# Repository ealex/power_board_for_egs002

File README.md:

# power_board_for_egs002
a power board for EGS002, bases on the SK68-100SA heatsink

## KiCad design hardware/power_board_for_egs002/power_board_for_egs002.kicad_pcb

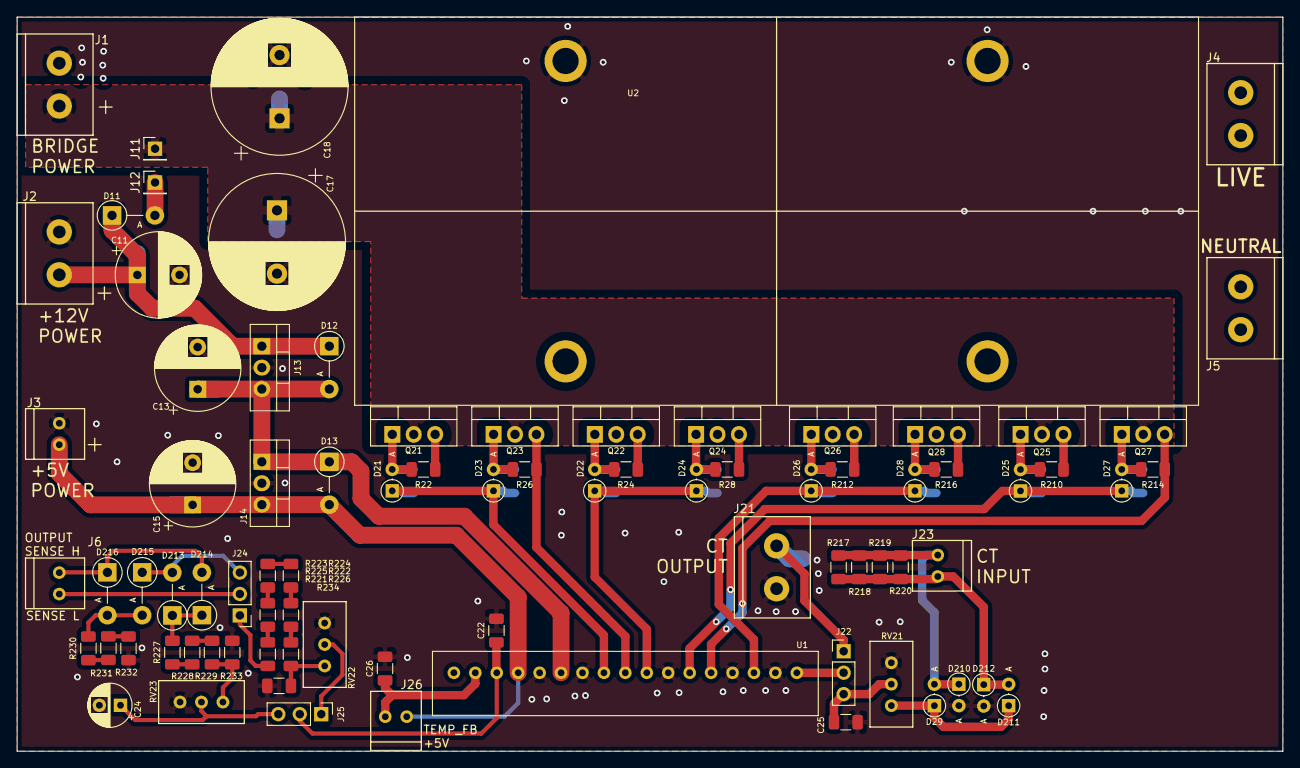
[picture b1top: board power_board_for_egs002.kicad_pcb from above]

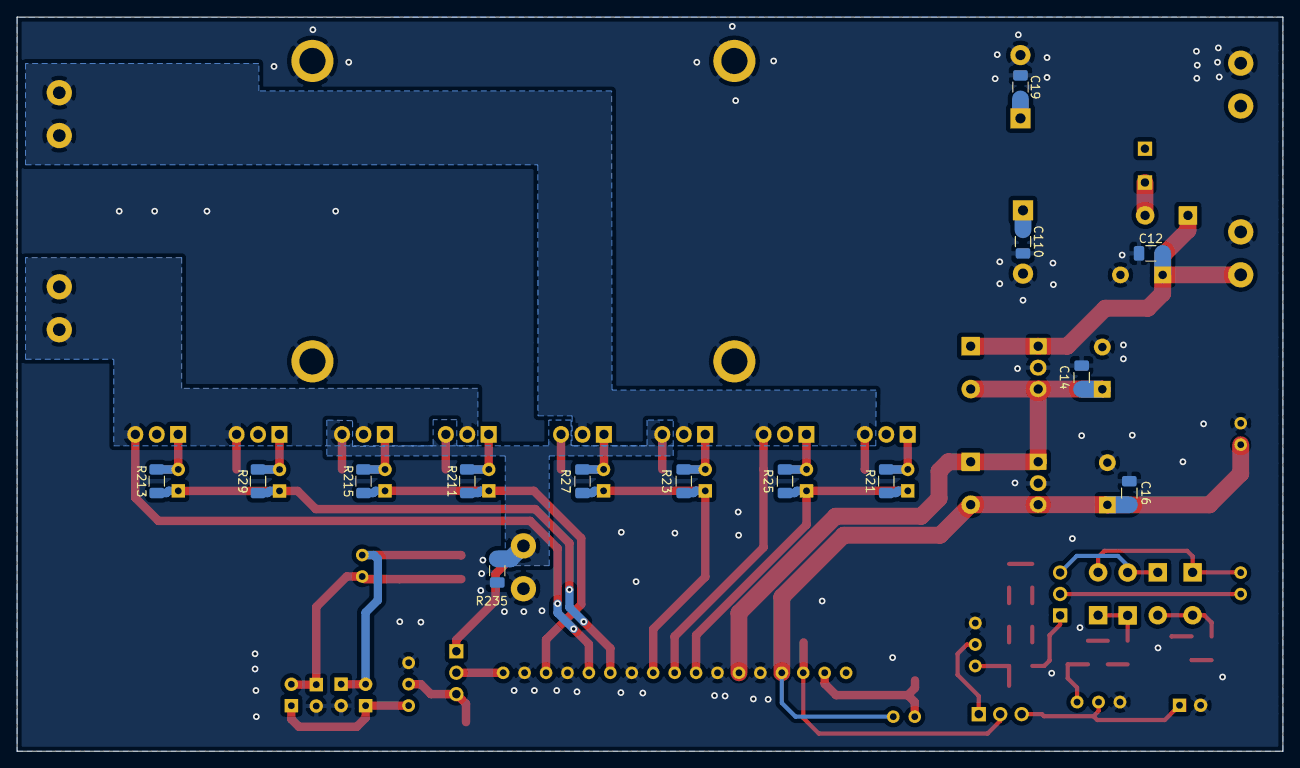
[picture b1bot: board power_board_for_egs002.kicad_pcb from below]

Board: 2 copper layers, 150.0 x 87.0 mm, 97 parts (14 on the bottom side), 47 nets.

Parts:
C11: B41858C5477M000; CP_Radial_D10.0mm_P5.00mm
C12, C14, C16, C19, C22, C25, C26, C110: 100n; C_1206_3216Metric
C13, C15: 220u; CP_Radial_D10.0mm_P5.00mm
C17, C18: MCKSK050M222J36S; CP_Radial_D16.0mm_P7.50mm
C24: 4.7u; CP_Radial_D5.0mm_P2.50mm
D11, D12, D13, D213, D214, D215, D216: 1N4007; D_DO-41_SOD81_P5.08mm_Vertical_AnodeUp
D21, D22, D23, D24, D25, D26, D27, D28, D29, D210, D211, D212: 1N4148; D_DO-35_SOD27_P2.54mm_Vertical_AnodeUp
J1: +HV; conn_5.08
J2: +12V; conn_5.08
J3: +5V; conn_2.54
J4: BRIGDE_OUT_2; conn_5.08
J5: BRIGDE_OUT_1; conn_5.08
J6: HV_SENSE; conn_2.54
J11, J12: +HV_TO_12; PinHeader_1x01_P2.54mm_Vertical
J13: HV_TO_12V; TO-220-3_Vertical
J14: 12V_TO_5V; TO-220-3_Vertical
J21: Conn_01x02; conn_5.08
J22: Conn_01x03; PinHeader_1x03_P2.54mm_Vertical
J23, J26: Conn_01x02; conn_2.54
J24: HV_SENSE_SELECT_A; PinHeader_1x03_P2.54mm_Vertical
J25: HV_SENSE_SELECT_B; PinHeader_1x03_P2.54mm_Vertical
Q21, Q22, Q23, Q24, Q25, Q26, Q27, Q28: TK40E06N1; TO-220-3_Vertical
R21, R23, R25, R27, R29, R211, R213, R215: 5.6; R_1206_3216Metric
R22, R24, R26, R28, R210, R212, R214, R216, R217, R218, R219, R220, R233, R234: 10k; R_1206_3216Metric
R221, R222, R223, R224, R225, R226, R227, R228, R229, R230, R231, R232: 33k; R_1206_3216Metric
R235: R_Small; R_1206_3216Metric
RV21, RV22, RV23: 100k; r_multiturn
U1: EGS002
U2: SK68-100SA

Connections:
/PowerBoard/1_HO: D25.1, D27.1, R29.1, R213.1, U1.6
/PowerBoard/1_LO: D26.1, D28.1, R211.1, R215.1, U1.3
/PowerBoard/1_VS: J5.1, J5.2, Q25.3, Q26.2, Q27.3, Q28.2, R210.1, R214.1, U1.5
/PowerBoard/2_HO: D21.1, D23.1, R21.2, R25.2, U1.10
/PowerBoard/2_LO: D22.1, D24.1, R23.2, R27.2, U1.8
/PowerBoard/2_VS: J4.1, J4.2, Q21.3, Q22.2, Q23.3, Q24.2, R22.1, R26.1, U1.9
/PowerBoard/HV_SENSE_L: J6.1, J24.2
/PowerBoard/HV_SENSE_N: D214.2, D216.1, J6.2
/PowerBoard/I_FB: J22.2, U1.1
/PowerBoard/T_FB: C26.1, J26.2, U1.16
/PowerBoard/V_FB: C22.1, J25.2, U1.15
/PowerSupply/+5V_IN: C15.1, C16.1, D13.2, J3.1, J14.3, J26.1, U1.14
/PowerSupply/+12V_IN: C11.1, C12.1, D11.1, D12.1, J2.1, J13.1
/PowerSupply/+12V_OUT: C13.1, C14.1, D12.2, D13.1, J13.3, J14.1, U1.12
/PowerSupply/+HV_IN: C17.1, C18.1, C19.1, C110.1, J1.1, J11.1, Q21.2, Q23.2, Q25.2, Q27.2
GND: C11.2, C12.2, C13.2, C14.2, C15.2, C16.2, C17.2, C18.2, C19.2, C22.2, C24.2, C25.2, C26.2, C110.2, D210.2, D212.2, J1.2, J2.2, J3.2, J13.2, J14.2, J21.1, R232.1, R233.1, R234.1, R235.2, RV21.3, RV22.3, RV23.3, U1.2, U1.4, U1.7, U1.11, U1.13, U2.1, U2.2, U2.3, U2.4
unnamed: C24.1, J25.3, RV23.2
unnamed: C25.1, J22.3, RV21.2
unnamed: D11.2, J12.1
unnamed: D21.2, Q21.1, R21.1, R22.2
unnamed: D22.2, Q22.1, R23.1, R24.2
unnamed: D23.2, Q23.1, R25.1, R26.2
unnamed: D24.2, Q24.1, R27.1, R28.2
unnamed: D25.2, Q25.1, R29.2, R210.2
unnamed: D26.2, Q26.1, R211.2, R212.2
unnamed: D27.2, Q27.1, R213.2, R214.2
unnamed: D28.2, Q28.1, R215.2, R216.2
unnamed: D29.2, D210.1, J23.1, R217.2, R218.2, R219.2, R220.2
unnamed: D29.1, D211.1, RV21.1
unnamed: D211.2, D212.1, J23.2, R217.1, R218.1, R219.1, R220.1
unnamed: D213.1, D214.1, R227.2
unnamed: D213.2, D215.1, J24.3
unnamed: D215.2, D216.2, R230.2
unnamed: J21.2, J22.1, Q22.3, Q24.3, Q26.3, Q28.3, R24.1, R28.1, R212.1, R216.1, R235.1
unnamed: J24.1, R221.2
unnamed: J25.1, RV22.2
unnamed: R221.1, R222.2
unnamed: R222.1, R223.2
unnamed: R223.1, R224.2
unnamed: R224.1, R225.2
unnamed: R225.1, R226.2
unnamed: R226.1, R234.2, RV22.1
unnamed: R227.1, R228.2
unnamed: R228.1, R229.2
unnamed: R229.1, R233.2, RV23.1
unnamed: R230.1, R231.2
unnamed: R231.1, R232.2

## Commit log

2021-12-07 add major components documentation
2021-12-07 start working on the schematic
2021-12-09 continue sch update
2021-12-10 start adding footprints
2021-12-11 add 3d model for heatsink
2021-12-11 update footprints
2021-12-11 continue sch dev
2021-12-14 continue pcb work
2021-12-15 update layout
2022-01-13 add ech. schematic
